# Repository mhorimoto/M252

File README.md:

# M252

TB2で使用したPICのシリアル出力をM302Kに接続するためのアダプタ。
M302Kの接続先はU1のHV側に接続する。

Arduino UNO側のD6,D7が接続対象となる。
接続速度は、19200bps。

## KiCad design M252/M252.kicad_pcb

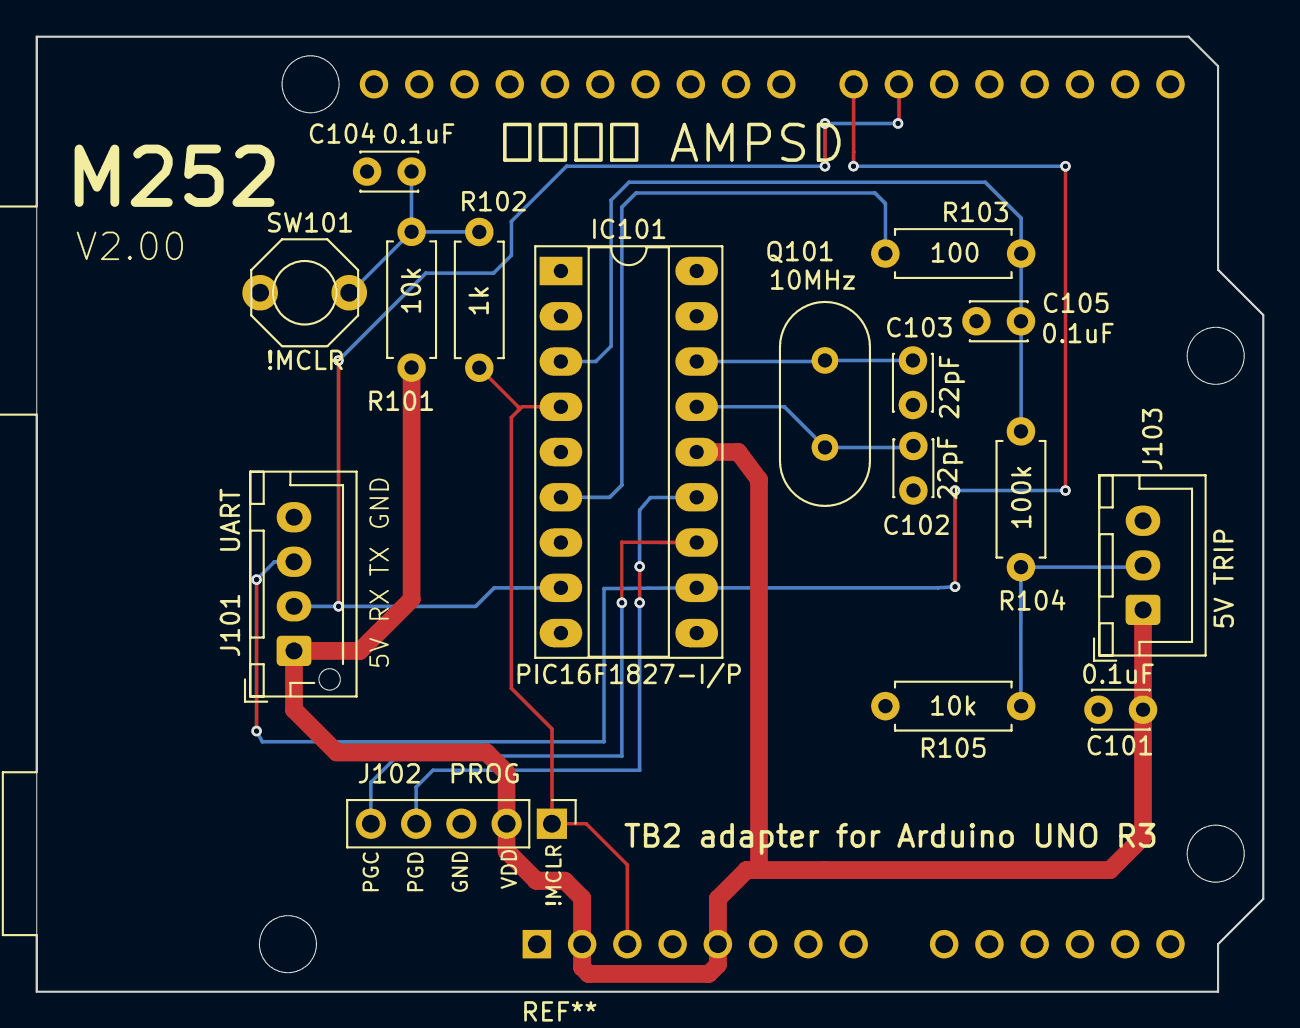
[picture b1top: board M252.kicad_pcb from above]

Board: 2 copper layers, 68.8 x 53.6 mm, 16 parts (0 on the bottom side), 13 nets.

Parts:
C101, C104, C105: 0.1uF; C_Disc_D3.0mm_W2.0mm_P2.50mm
C102, C103: 22pF; C_Disc_D3.0mm_W2.0mm_P2.50mm
IC101: PIC16F1827-I/P; DIP-18_W7.62mm_Socket_LongPads
J101: UART; JST_XH_B4B-XH-AM_1x04_P2.50mm_Vertical
J102: PROG; PinHeader_1x05_P2.54mm_Vertical
J103: TRIP; JST_XH_B3B-XH-A_1x03_P2.50mm_Vertical
Q101: 10MHz; Crystal_HC49-4H_Vertical
R101, R105: 10k; R_Axial_DIN0207_L6.3mm_D2.5mm_P7.62mm_Horizontal
R102: 1k; R_Axial_DIN0207_L6.3mm_D2.5mm_P7.62mm_Horizontal
R103: 100; R_Axial_DIN0207_L6.3mm_D2.5mm_P7.62mm_Horizontal
R104: 100k; R_Axial_DIN0207_L6.3mm_D2.5mm_P7.62mm_Horizontal
SW101: !MCLR; TVDT18-050

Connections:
+5V: C101.2, IC101.14 (VDD), J101.1, J102.2, J103.1, R101.2
/TB2_RX: IC101.8 (RB2), J101.2
/TB2_TX: IC101.11 (RB5), J101.3
GND: C101.1, C102.2, C103.2, C104.2, C105.2, IC101.5 (VSS), J101.4, J102.3, R105.2, SW101.2
unnamed: C104.1, R101.1, R102.2, SW101.1
unnamed: C105.1, IC101.3 (RA4), R103.1, R104.2
unnamed: IC101.4 (RA5/~MCLR/VPP), J102.1, R102.1
unnamed: C102.1, IC101.15 (RA6), Q101.2
unnamed: C103.1, IC101.16 (RA7), Q101.1
unnamed: IC101.6 (RB0), R103.2
unnamed: IC101.12 (RB6), J102.5
unnamed: IC101.13 (RB7), J102.4
unnamed: J103.2, R104.1, R105.1

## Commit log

2024-12-08 Real first commit
2024-12-10 v1.01 ガーバー出力
2024-12-12 VOLTERA
2024-12-13 VOLTERA Version
2024-12-14 とりあえず後で見直す
2025-01-20 PCB発注前DRC済
2025-01-20 UNO直結タイプ1st
2025-01-20 M252オリジナルPCB発注
2025-01-29 PCB完成
2025-03-10 資料追加
2025-03-30 LCDパーツ仕様書追加
